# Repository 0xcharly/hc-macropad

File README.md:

<div align="center">

</div>

---

# HC Macropad

PCB for HC Macropad event.

## BOM

- 1× EC11 rotary encoder
- 6× MX switches
- 6× SOD123 diodes
- (optional) 12× SK6812 Mini-E LEDs

## 3D Model

The 3D model was designed with [OnShape](https://onshape.com) and is available
[publicly](https://cad.onshape.com/documents/3070554cf94c5dc376b0a8a4/w/4d0968bd551d0635d2f8d7e6/e/86d2deca2d0d715bf15eadd2?renderMode=0&uiState=67038575d1a53e07c780a03b).

## Firmware

The firmware is powered by [QMK](https://qmk.fm) and can be found in
[0xcharly/qmk_firmware](https://github.com/0xcharly/qmk_firmware/tree/hc-macropad)
on the `hc-macropad` branch.

The keyboard and keymap are defined under `keyboards/hc_macropad` and can be
built using the QMK CLI:

```sh
qmk compile -kb hc_macropad -km default
```

See the
[README.md](https://github.com/0xcharly/qmk_firmware/blob/hc-macropad/keyboards/hc_macropad/readme.md)
for more information.

## First prototypes

The encoder case footprint needs some work…

## Credits

The PCB design, and specifically the RP2040-based controller is based off the
work of [Bastard Keyboards](https://bastardkb.com), adapted from their
[Dilemma](https://github.com/Bastardkb/Dilemma) design.

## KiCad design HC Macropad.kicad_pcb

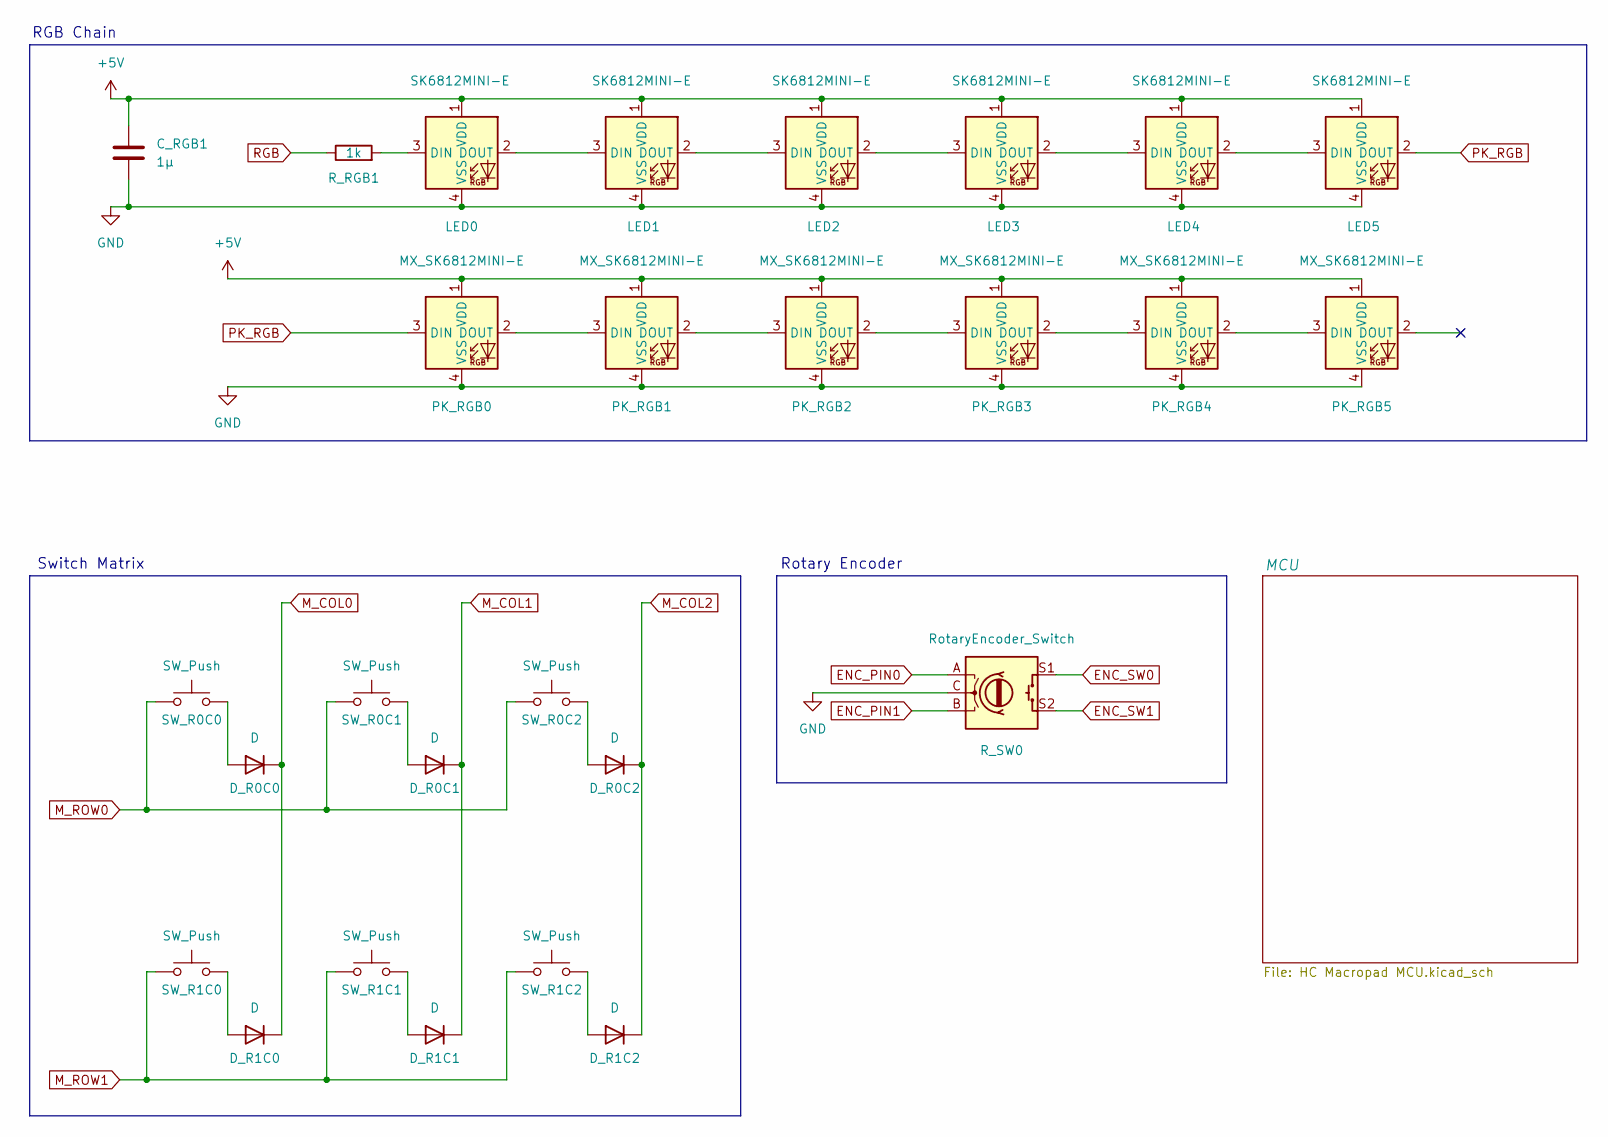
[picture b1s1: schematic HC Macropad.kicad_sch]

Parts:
C_RGB1: 1µ; C_0402_1005Metric; LCSC C52923
D_R0C0, D_R0C1, D_R0C2, D_R1C0, D_R1C1, D_R1C2: D; D_SOD-123; LCSC C571353
LED0, LED1, LED2, LED3, LED4, LED5: SK6812MINI-E; LED_6028R; LCSC C5149201
PK_RGB0, PK_RGB1, PK_RGB2, PK_RGB3, PK_RGB4, PK_RGB5: MX_SK6812MINI-E; LED_MX_6028R; LCSC C5149201
R_RGB1: 1k; R_0402_1005Metric; LCSC C11702
R_SW0: RotaryEncoder_Switch; RotaryEncoder_Alps_EC11E-Switch_Vertical_H20mm
SW_R0C0, SW_R0C1, SW_R0C2, SW_R1C0, SW_R1C1, SW_R1C2: SW_Push; SW_MX_1u

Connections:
+5V: C_RGB1.1, LED0.1 (VDD), LED1.1 (VDD), LED2.1 (VDD), LED3.1 (VDD), LED4.1 (VDD), LED5.1 (VDD), PK_RGB0.1 (VDD), PK_RGB1.1 (VDD), PK_RGB2.1 (VDD), PK_RGB3.1 (VDD), PK_RGB4.1 (VDD), PK_RGB5.1 (VDD); also elsewhere on the board
ENC_PIN0: R_SW0.A; also elsewhere on the board
ENC_PIN1: R_SW0.B; also elsewhere on the board
ENC_SW0: R_SW0.S1; also elsewhere on the board
ENC_SW1: R_SW0.S2; also elsewhere on the board
GND: C_RGB1.2, LED0.4 (VSS), LED1.4 (VSS), LED2.4 (VSS), LED3.4 (VSS), LED4.4 (VSS), LED5.4 (VSS), PK_RGB0.4 (VSS), PK_RGB1.4 (VSS), PK_RGB2.4 (VSS), PK_RGB3.4 (VSS), PK_RGB4.4 (VSS), PK_RGB5.4 (VSS), R_SW0.C; also elsewhere on the board
M_COL0: D_R0C0.1 (K), D_R1C0.1 (K); also elsewhere on the board
M_COL1: D_R0C1.1 (K), D_R1C1.1 (K); also elsewhere on the board
M_COL2: D_R0C2.1 (K), D_R1C2.1 (K); also elsewhere on the board
M_ROW0: SW_R0C0.1, SW_R0C1.1, SW_R0C2.1; also elsewhere on the board
M_ROW1: SW_R1C0.1, SW_R1C1.1, SW_R1C2.1; also elsewhere on the board
unnamed: D_R0C0.2 (A), SW_R0C0.2
unnamed: D_R0C1.2 (A), SW_R0C1.2
unnamed: D_R0C2.2 (A), SW_R0C2.2
unnamed: D_R1C0.2 (A), SW_R1C0.2
unnamed: D_R1C1.2 (A), SW_R1C1.2
unnamed: D_R1C2.2 (A), SW_R1C2.2
unnamed: LED0.3 (DIN), R_RGB1.2
unnamed: LED0.2 (DOUT), LED1.3 (DIN)
unnamed: LED1.2 (DOUT), LED2.3 (DIN)
unnamed: LED2.2 (DOUT), LED3.3 (DIN)
unnamed: LED3.2 (DOUT), LED4.3 (DIN)
unnamed: LED4.2 (DOUT), LED5.3 (DIN)
unnamed: PK_RGB0.2 (DOUT), PK_RGB1.3 (DIN)
unnamed: PK_RGB1.2 (DOUT), PK_RGB2.3 (DIN)
unnamed: PK_RGB2.2 (DOUT), PK_RGB3.3 (DIN)
unnamed: PK_RGB3.2 (DOUT), PK_RGB4.3 (DIN)
unnamed: PK_RGB4.2 (DOUT), PK_RGB5.3 (DIN)
PK_RGB: LED5.2 (DOUT), PK_RGB0.3 (DIN)
RGB: R_RGB1.1; also elsewhere on the board

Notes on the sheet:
Switch Matrix
RGB Chain
Rotary Encoder

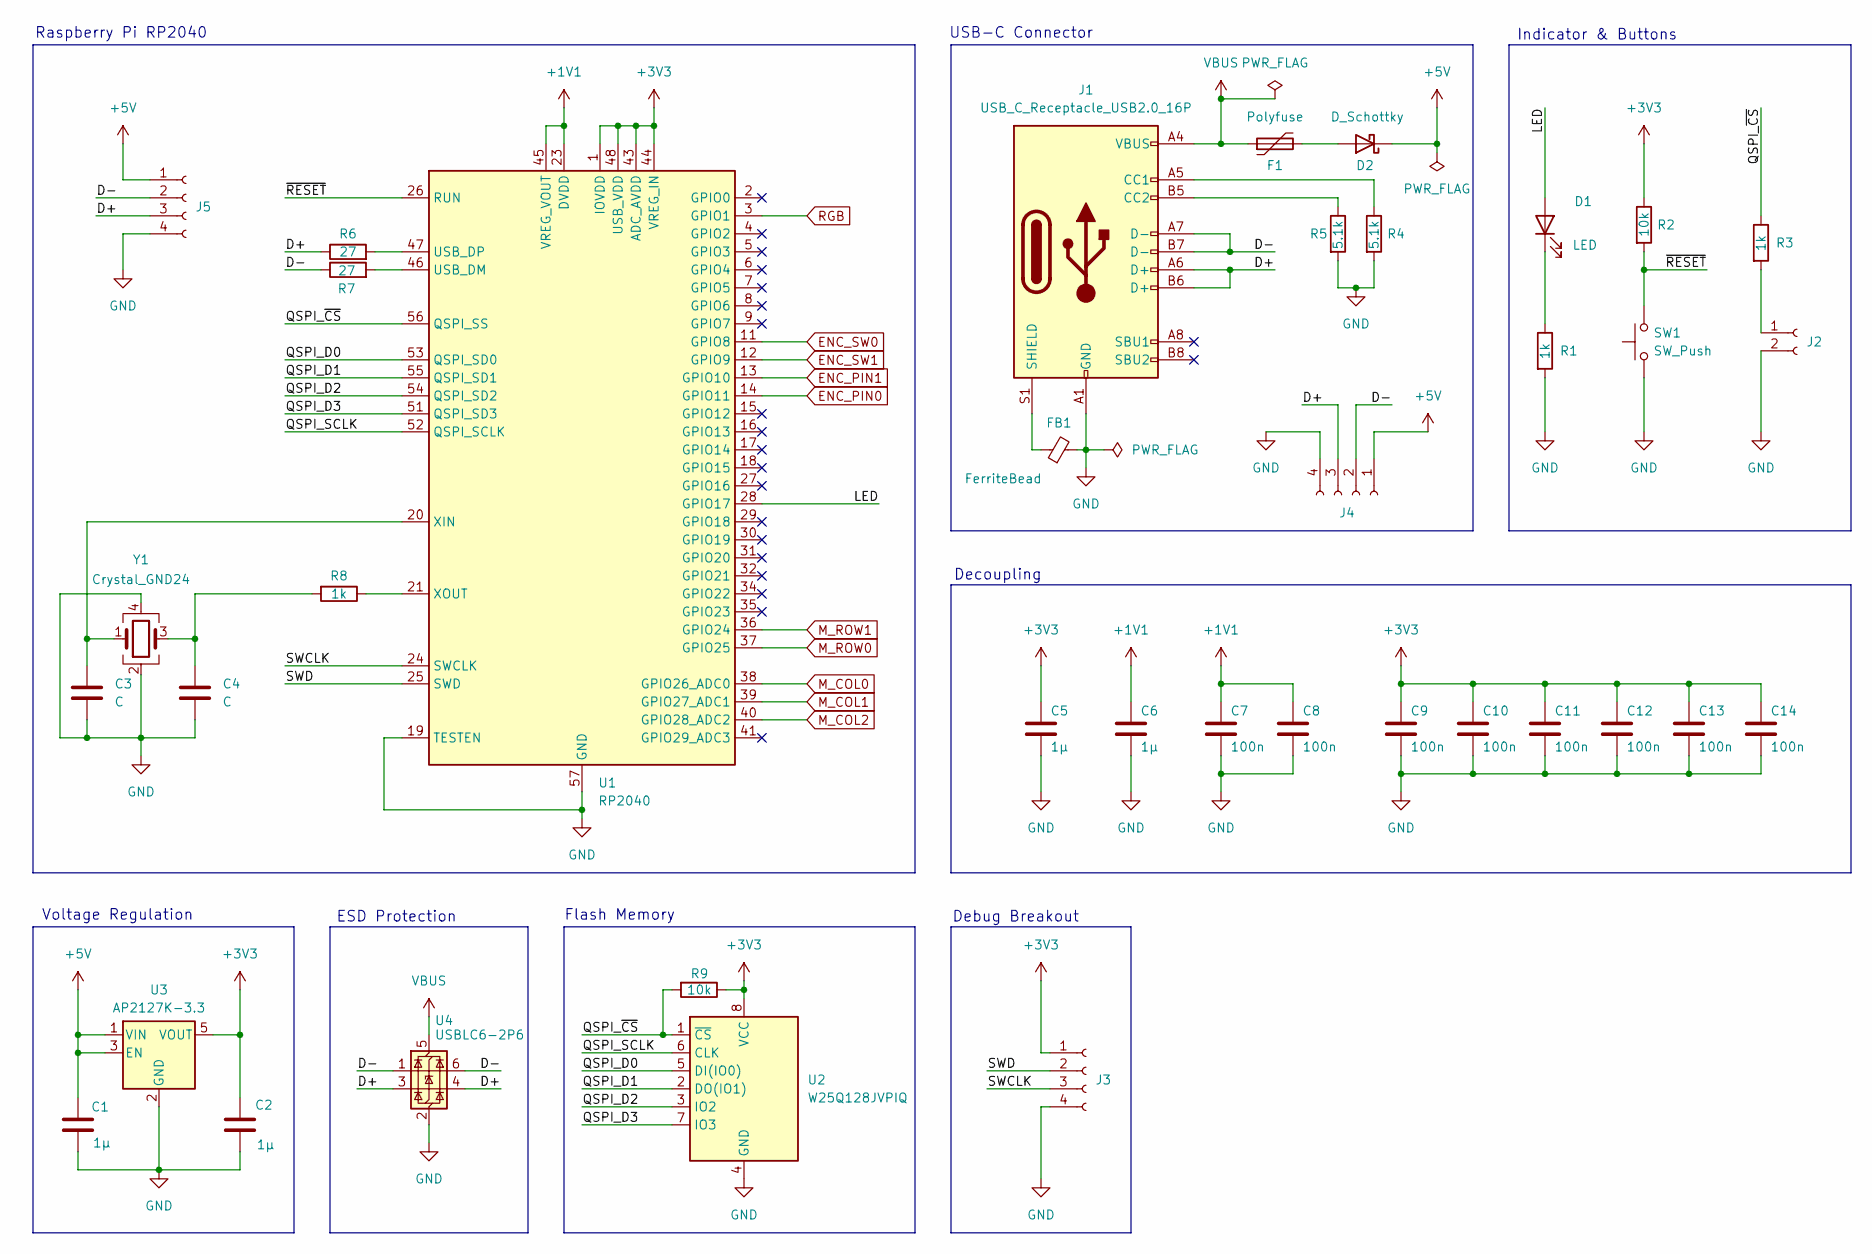
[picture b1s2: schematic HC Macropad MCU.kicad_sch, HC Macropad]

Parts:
C1, C2: 1µ; C_0603_1608Metric; LCSC C19666
C3, C4: C; C_0402_1005Metric; LCSC C1548
C5, C6: 1µ; C_0402_1005Metric; LCSC C52923
C7, C8, C9, C10, C11, C12, C13, C14: 100n; C_0402_1005Metric; LCSC C1525
D1: LED; LED_0402_1005Metric; LCSC C130719
D2: D_Schottky; D_SOD-323; LCSC C123899
F1: Polyfuse; Fuse_0603_1608Metric; LCSC C69679
FB1: FerriteBead; L_0603_1608Metric; LCSC C98288
J1: USB_C_Receptacle_USB2.0_16P; USB_C_Receptacle_HRO_TYPE-C-31-M-12; LCSC C165948
J2: Conn_01x02_Socket; PinHeader_1x02_P1.27mm_Vertical
J3, J4, J5: Conn_01x04_Socket; PinHeader_1x04_P2.54mm_Vertical
R1, R3, R8: 1k; R_0402_1005Metric; LCSC C11702
R2, R9: 10k; R_0402_1005Metric; LCSC C25744
R4, R5: 5.1k; R_0402_1005Metric; LCSC C25905
R6, R7: 27; R_0402_1005Metric; LCSC C25100
SW1: SW_Push; SW_SPST_CK_KXT3; LCSC C319433
U1: RP2040; QFN-56-1EP_7x7mm_P0.4mm_EP3.2x3.2mm; LCSC C2040
U2: W25Q128JVPIQ; WSON-8-1EP_6x5mm_P1.27mm_EP3.4x4.3mm; LCSC C190862
U3: AP2127K-3.3; SOT-23-5; LCSC C82942
U4: USBLC6-2P6; SOT-666; LCSC C2827693
Y1: Crystal_GND24; Crystal_SMD_2520-4Pin_2.5x2.0mm; LCSC C2149204

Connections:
+1V1: C6.1, C7.1, C8.1, U1.23 (DVDD), U1.45 (VREG_VOUT), U1.50 (DVDD)
+3V3: C2.1, C5.1, C9.1, C10.1, C11.1, C12.1, C13.1, C14.1, J3.1, R2.1, R9.1, U1.1 (IOVDD), U1.10 (IOVDD), U1.22 (IOVDD), U1.33 (IOVDD), U1.42 (IOVDD), U1.43 (ADC_AVDD), U1.44 (VREG_IN), U1.48 (USB_VDD), U1.49 (IOVDD), U2.8 (VCC), U3.5 (VOUT)
+5V: C1.1, D2.1 (K), J4.1, J5.1, U3.1 (VIN), U3.3 (EN); also elsewhere on the board
/MCU/D+: J1.A6 (D+), J1.B6 (D+), J4.3, J5.3, R6.1, U4.3 (I/O2), U4.4 (I/O2)
/MCU/D-: J1.A7 (D-), J1.B7 (D-), J4.2, J5.2, R7.1, U4.1 (I/O1), U4.6 (I/O1)
/MCU/LED: D1.2 (A), U1.28 (GPIO17)
/MCU/QSPI_D0: U1.53 (QSPI_SD0), U2.5 (DI(IO0))
/MCU/QSPI_D1: U1.55 (QSPI_SD1), U2.2 (DO(IO1))
/MCU/QSPI_D2: U1.54 (QSPI_SD2), U2.3 (IO2)
/MCU/QSPI_D3: U1.51 (QSPI_SD3), U2.7 (IO3)
/MCU/QSPI_SCLK: U1.52 (QSPI_SCLK), U2.6 (CLK)
/MCU/QSPI_~CS: R3.1, R9.2, U1.56 (QSPI_SS), U2.1 (~CS)
/MCU/SWCLK: J3.3, U1.24 (SWCLK)
/MCU/SWD: J3.2, U1.25 (SWD)
/MCU/~RESET: R2.2, SW1.2, U1.26 (RUN)
ENC_PIN0: U1.14 (GPIO11); also elsewhere on the board
ENC_PIN1: U1.13 (GPIO10); also elsewhere on the board
ENC_SW0: U1.11 (GPIO8); also elsewhere on the board
ENC_SW1: U1.12 (GPIO9); also elsewhere on the board
GND: C1.2, C2.2, C3.2, C4.2, C5.2, C6.2, C7.2, C8.2, C9.2, C10.2, C11.2, C12.2, C13.2, C14.2, FB1.2, J1.A1 (GND), J1.A12 (GND), J1.B1 (GND), J1.B12 (GND), J2.2, J3.4, J4.4, J5.4, R1.2, R4.2, R5.2, SW1.1, U1.19 (TESTEN), U1.57 (GND), U2.4 (GND), U3.2 (GND), U4.2 (GND), Y1.2, Y1.4; also elsewhere on the board
M_COL0: U1.38 (GPIO26_ADC0); also elsewhere on the board
M_COL1: U1.39 (GPIO27_ADC1); also elsewhere on the board
M_COL2: U1.40 (GPIO28_ADC2); also elsewhere on the board
M_ROW0: U1.37 (GPIO25); also elsewhere on the board
M_ROW1: U1.36 (GPIO24); also elsewhere on the board
unnamed: C4.1, R8.2, Y1.3
unnamed: D1.1 (K), R1.1
unnamed: D2.2 (A), F1.2
unnamed: J1.A5 (CC1), R4.1
unnamed: J1.B5 (CC2), R5.1
unnamed: FB1.1, J1.S1 (SHIELD)
unnamed: J2.1, R3.2
unnamed: R7.2, U1.46 (USB_DM)
unnamed: R6.2, U1.47 (USB_DP)
unnamed: C3.1, U1.20 (XIN), Y1.1
unnamed: R8.1, U1.21 (XOUT)
RGB: U1.3 (GPIO1); also elsewhere on the board
VBUS: F1.1, J1.A4 (VBUS), J1.A9 (VBUS), J1.B4 (VBUS), J1.B9 (VBUS), U4.5 (VBUS)

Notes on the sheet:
Indicator & Buttons
Voltage Regulation
Flash Memory
Raspberry Pi RP2040
Decoupling
ESD Protection
Debug Breakout
USB-C Connector

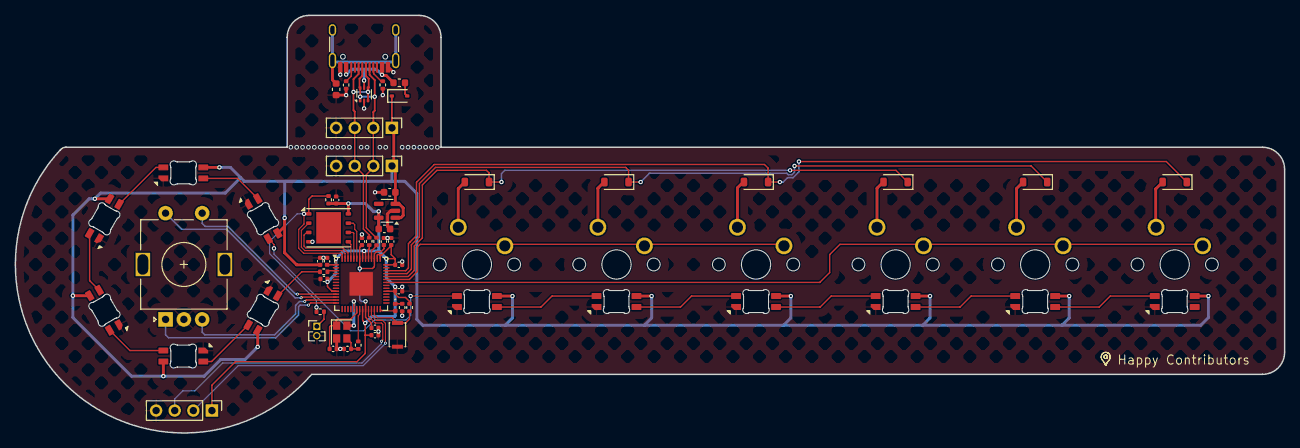
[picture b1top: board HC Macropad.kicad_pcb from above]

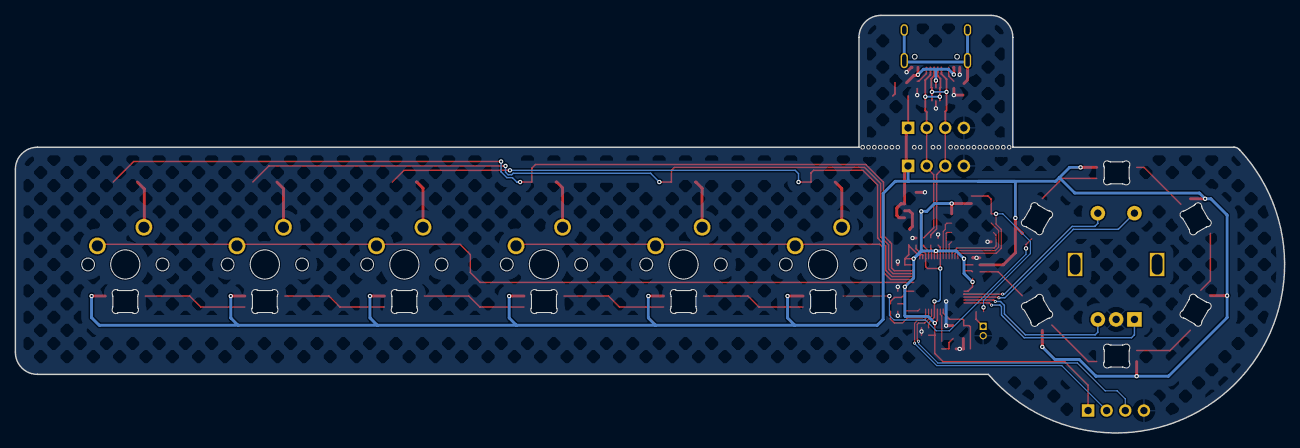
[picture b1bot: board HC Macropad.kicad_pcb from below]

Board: 2 copper layers, 173.2 x 57.0 mm, 65 parts (6 on the bottom side), 56 nets.

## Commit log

2024-10-02 Initial commit: v0.1.1
2024-10-02 Add lock files to gitignore
2024-10-03 Starting to work on the PCB, might need to enlarge it
2024-10-05 Move switches, diodes, and LEDs to their final location
2024-10-06 90% of routing done
2024-10-06 Finished routing
2024-10-06 Remove all remaining warnings
2024-10-07 Pack flash a little bit more closer to the rest of the MCU components to give as much clearance to the handsolder components as possible
2024-10-07 Minor trace touch up
2024-10-07 Update comments and LICENCE file to CERN Open Hardware Licence v2
2024-10-07 Mark connectors as 'Do not populate'
2024-10-07 Use English spelling for the LICENSE filename
2024-10-07 Add pictures
2024-10-07 Fix badge in README.md
2024-10-07 Minor routing changes
2024-10-07 Minor changes before production
2024-10-16 Update `README.md` with f/w instructions
2024-10-16 Add pictures of first prototypes
2024-10-16 I'm hilarious…
2024-10-30 v0.1.3: UFE edition
2024-10-30 v0.1.4: HC edition
2024-10-31 v0.1.5: finalized HC edition

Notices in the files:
HC Macropad MCU.kicad_sch:
Licensed under CERN-OHL-W v2
README.md:
License: CERN OHL V2
